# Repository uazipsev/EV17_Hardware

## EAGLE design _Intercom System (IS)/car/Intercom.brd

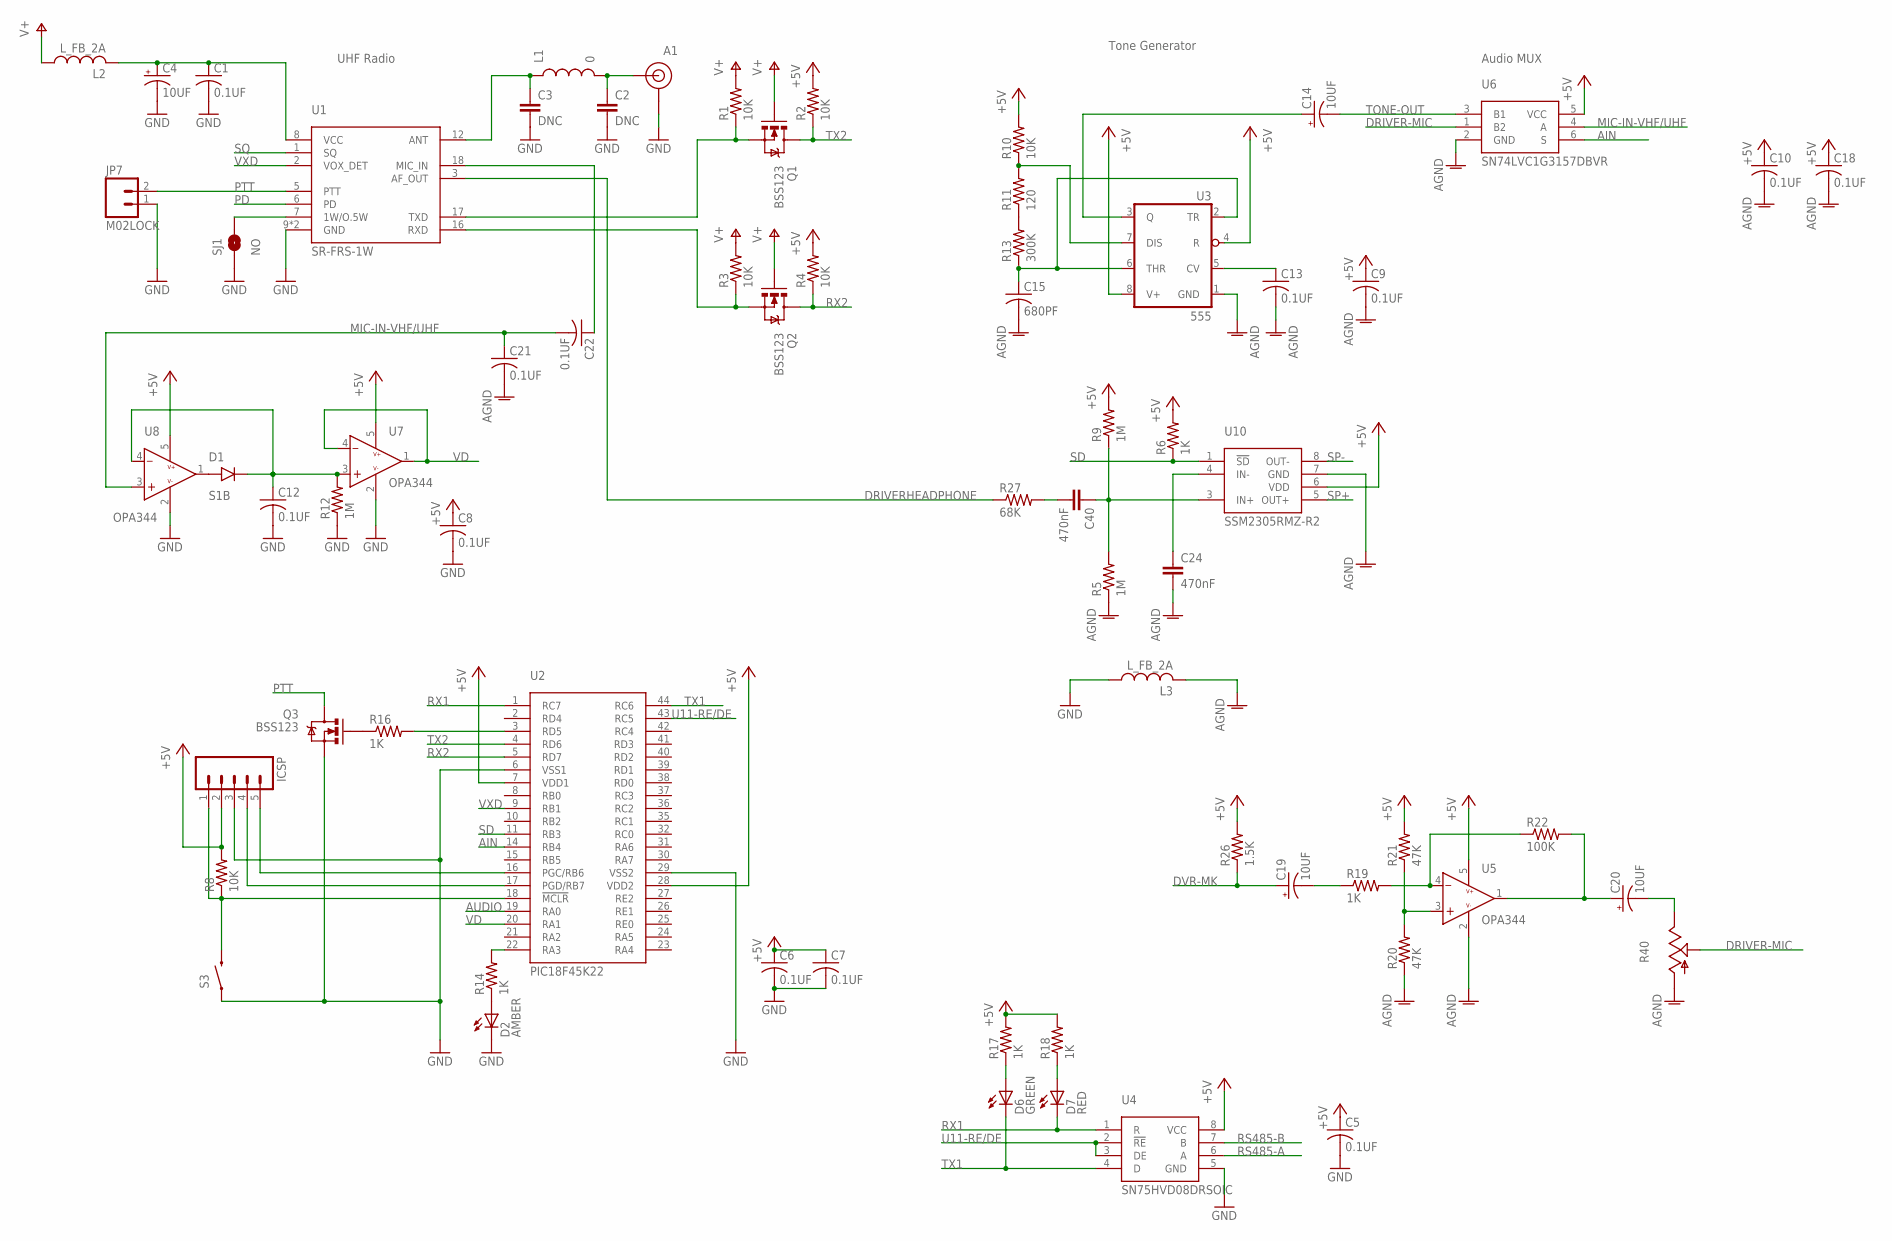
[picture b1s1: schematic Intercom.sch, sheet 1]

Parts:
A1: CONSMA003.062
C1, C5, C6, C7, C8, C9, C10, C12, C13, C18, C21, C22: 0.1UF; 0805
C2, C3: DNC; 0805
C4, C14, C19, C20: 10UF; EIA3216-16V
C15: 680PF; 0805
C24, C40: 470nF; 0805
D1: S1B; SMA
D2: AMBER; CHIP_LED0805
D6: GREEN; CHIP_LED0805
D7: RED; CHIP_LED0805
ICSP: M05LOCK_LONGPADS; 1X05_LOCK_LONGPADS
JP7: M02LOCK; 1X02_LOCK
L1: 0; 1007
L2, L3: L_FB_2A; 0805
Q1, Q2, Q3: BSS123; SOT23
R1, R2, R3, R4, R8, R10: 10K; 0805
R5, R9, R12: 1M; 0805
R6, R14, R16, R17, R18, R19: 1K; 0805
R11: 120; 0805
R13: 300K; 0805
R20, R21: 47K; 0805
R22: 100K; 0805
R26: 1.5K; 0805
R27: 68K; 0805
R40: TRIM_US-CA6H; CA6H
S3: SWITCH-MOMENTARY-2SIDE_EZ; TACTILE-PTH-SIDEEZ
SJ1: NO; SJ_2S-NO
U1: SR-FRS-1W
U2: PIC18F45K22; TQFP-44
U3: 555; SO-8
U4: SN75HVD08DRSOIC; SO-8
U5, U7, U8: OPA344; SOT23-5
U6: SN74LVC1G3157DBVR; SOT23-6
U10: SSM2305RMZ-R2; MSOP-8

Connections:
+5V: C5.1 (+), C6.1 (+), C7.1 (+), C8.1 (+), C9.1 (+), C10.1 (+), C18.1 (+), ICSP.2, R2.2, R4.2, R6.2, R8.2, R9.2, R10.2, R17.2, R18.2, R21.2, R26.2, U2.7 (VDD1), U2.28 (VDD2), U3.4 (R), U3.8 (V+), U4.8 (VCC), U5.5 (V+), U6.5 (VCC), U7.5 (V+), U8.5 (V+), U10.6 (VDD); also elsewhere on the board
AGND: C9.2 (-), C10.2 (-), C13.2 (-), C15.2 (-), C18.2 (-), C21.2 (-), C24.2, L3.2, R5.1, R20.1, R40.A, U3.1 (GND), U5.2 (V-), U6.2 (GND), U10.7 (GND); also elsewhere on the board
AIN: U2.14 (RB4), U6.6 (S)
AUDIO: U2.19 (RA0)
DRIVER-MIC: R40.S, U6.1 (B2)
DRIVERHEADPHONE: R27.1, U1.3 (AF_OUT)
DVR-MK: C19.A (+), R26.1; also elsewhere on the board
GND: A1.G (GND), A1.G1 (GND), A1.G2 (GND), A1.G3 (GND), C1.2 (-), C2.2, C3.2, C4.C (-), C5.2 (-), C6.2 (-), C7.2 (-), C8.2 (-), C12.2 (-), D2.C, ICSP.3, JP7.1, L3.1, Q3.2 (S), R12.1, S3.1, SJ1.1, U1.9 (GND), U1.10 (GND), U2.6 (VSS1), U2.29 (VSS2), U4.5 (GND), U7.2 (V-), U8.2 (V-); also elsewhere on the board
MIC-IN-VHF/UHF: C21.1 (+), C22.2 (-), U6.4 (A), U8.3 (+)
unnamed: C3.1, L1.1, U1.12 (ANT)
unnamed: A1.S (SIGNAL), C2.1, L1.2
unnamed: C1.1 (+), C4.A (+), L2.2, U1.8 (VCC)
unnamed: SJ1.2, U1.7 (1W/O.5W)
unnamed: D1.A, U8.1 (O)
unnamed: C15.1 (+), R13.1, U3.2 (TR), U3.6 (THR)
unnamed: Q2.2 (S), R3.1, U1.16 (RXD)
unnamed: Q1.2 (S), R1.1, U1.17 (TXD)
unnamed: D2.A, R14.1
unnamed: C13.1 (+), U3.5 (CV)
unnamed: R10.1, R11.2, U3.7 (DIS)
unnamed: C24.1, U10.4 (IN-)
unnamed: Q3.1 (G), R16.1
unnamed: R20.2, R21.1, U5.3 (+)
unnamed: C14.A (+), U3.3 (Q)
unnamed: R16.2, U2.3 (RD5)
unnamed: C20.C (-), R40.E
unnamed: C12.1 (+), D1.C, R12.2, U7.3 (+), U8.4 (-)
unnamed: R11.1, R13.2
unnamed: R14.2, U2.22 (RA3)
unnamed: C20.A (+), R22.2, U5.1 (O)
unnamed: R19.2, R22.1, U5.4 (-)
unnamed: C19.C (-), R19.1
unnamed: C40.1, R5.2, R9.1, U10.3 (IN+)
unnamed: ICSP.4, U2.17 (PGD/RB7)
unnamed: ICSP.5, U2.16 (PGC/RB6)
unnamed: C40.2, R27.2
unnamed: ICSP.1, R8.1, S3.2, U2.18 (!MCLR)
unnamed: C22.1 (+), U1.18 (MIC_IN)
unnamed: D7.A, R18.1
unnamed: D6.A, R17.1
PD: U1.6 (PD)
PTT: JP7.2, Q3.3 (D), U1.5 (PTT)
RS485-A: U4.6 (A); also elsewhere on the board
RS485-B: U4.7 (B); also elsewhere on the board
RX1: D7.C, U2.1 (RC7), U4.1 (R)
RX2: Q2.3 (D), R4.1, U2.5 (RD7)
SD: R6.1, U2.11 (RB3), U10.1 (!SD)
SP+: U10.5 (OUT+); also elsewhere on the board
SP-: U10.8 (OUT-); also elsewhere on the board
SQ: U1.1 (SQ)
TONE-OUT: C14.C (-), U6.3 (B1)
TX1: D6.C, U2.44 (RC6), U4.4 (D)
TX2: Q1.3 (D), R2.1, U2.4 (RD6)
U11-RE/DE: U2.43 (RC5), U4.2 (!RE), U4.3 (DE)
V+: L2.1, Q1.1 (G), Q2.1 (G), R1.2, R3.2; also elsewhere on the board
VD: U2.20 (RA1), U7.1 (O), U7.4 (-)
VXD: U1.2 (VOX_DET), U2.9 (RB1)

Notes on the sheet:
UHF Radio
Tone Generator
Audio MUX

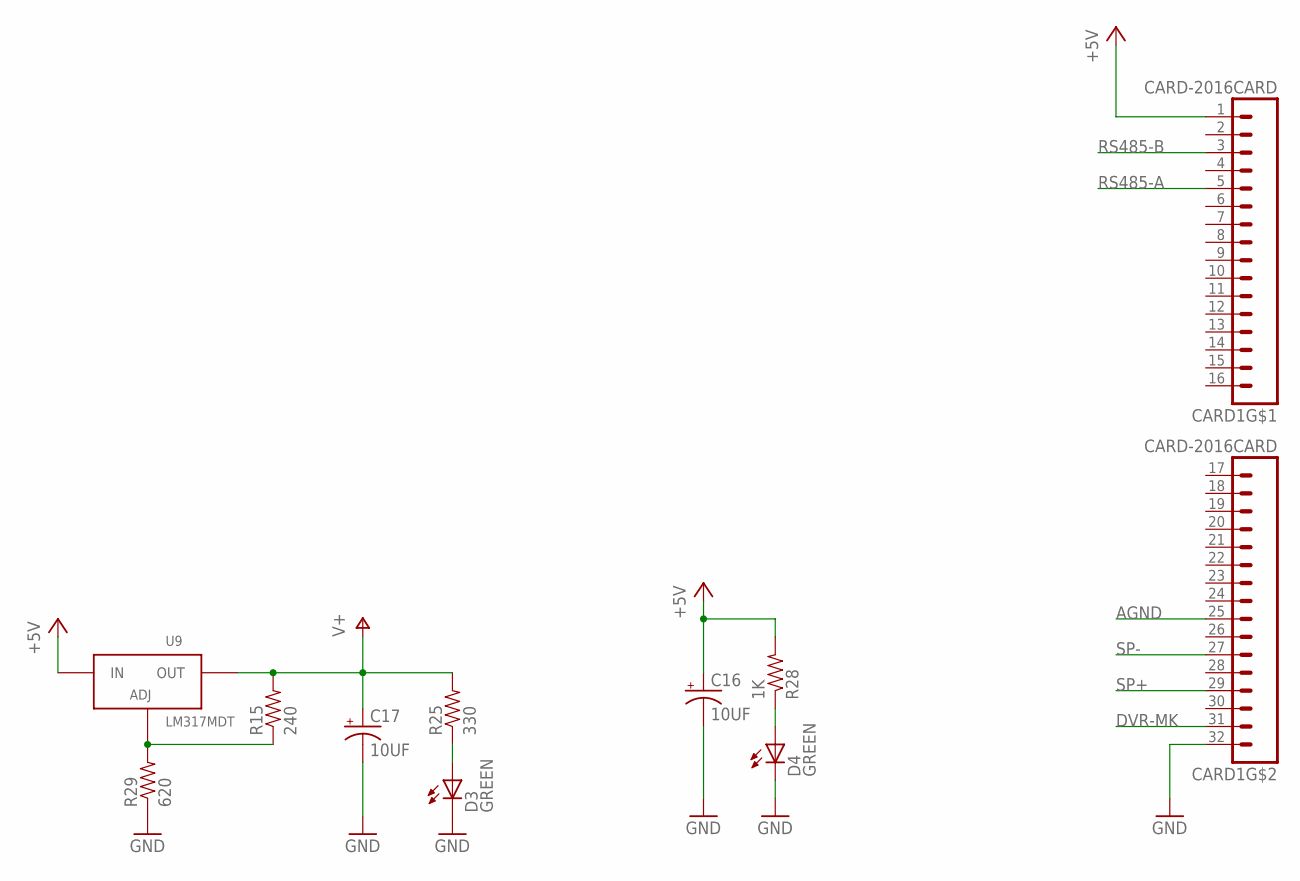
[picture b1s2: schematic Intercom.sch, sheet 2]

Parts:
C16, C17: 10UF; EIA3216-16V
CARD1: CARD-2016CARD; CARD-2016
D3, D4: GREEN; CHIP_LED0805
R15: 240; 0805
R25: 330; 0805
R28: 1K; 0805
R29: 620; 0805
U9: LM317MDT; DPAK

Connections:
+5V: C16.A (+), CARD1.1, R28.2, U9.2 (IN); also elsewhere on the board
AGND: CARD1.25 (9); also elsewhere on the board
DVR-MK: CARD1.31 (15); also elsewhere on the board
GND: C16.C (-), C17.C (-), CARD1.32 (16), D3.C, D4.C, R29.1; also elsewhere on the board
unnamed: R15.1, R29.2, U9.1 (ADJ)
unnamed: D4.A, R28.1
unnamed: D3.A, R25.1
RS485-A: CARD1.5; also elsewhere on the board
RS485-B: CARD1.3; also elsewhere on the board
SP+: CARD1.29 (13); also elsewhere on the board
SP-: CARD1.27 (11); also elsewhere on the board
V+: C17.A (+), R15.2, R25.2, U9.3 (OUT); also elsewhere on the board

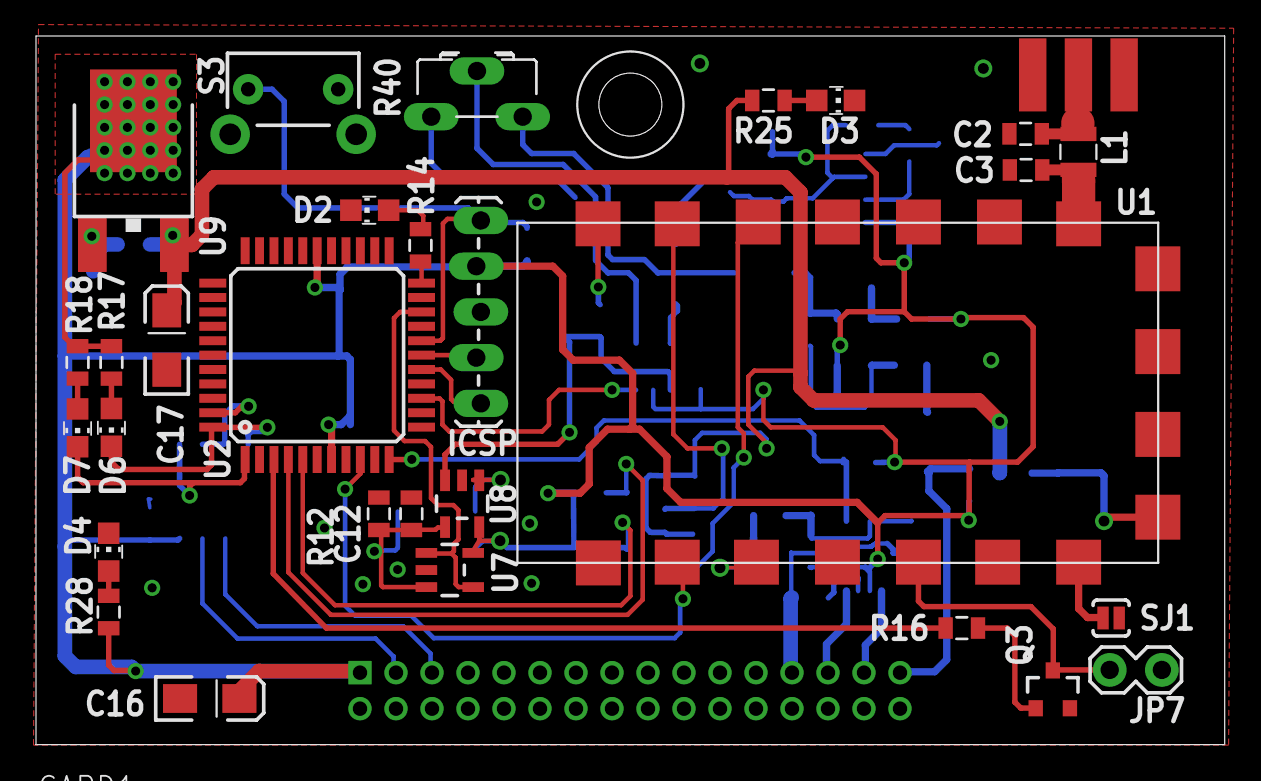
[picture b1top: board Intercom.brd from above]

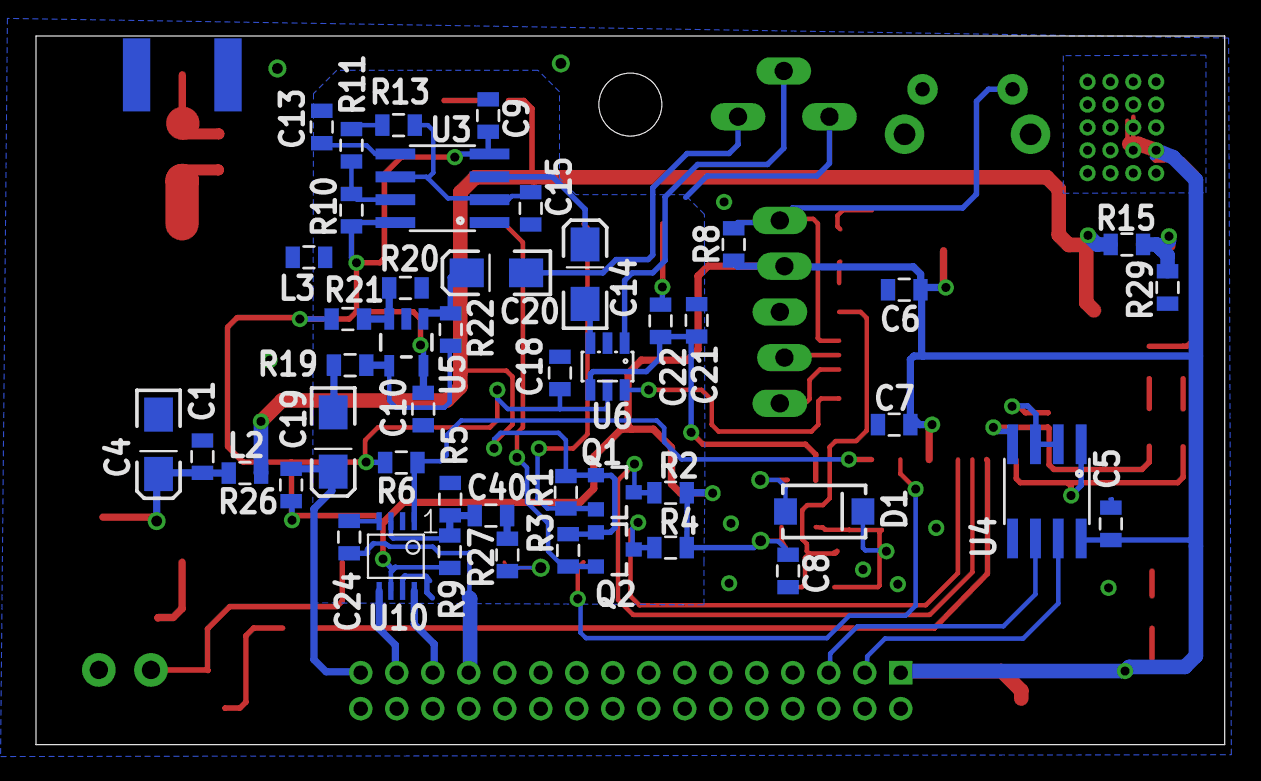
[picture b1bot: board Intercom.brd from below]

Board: 2 copper layers, 66.0 x 39.4 mm, 78 parts (47 on the bottom side), 57 nets.

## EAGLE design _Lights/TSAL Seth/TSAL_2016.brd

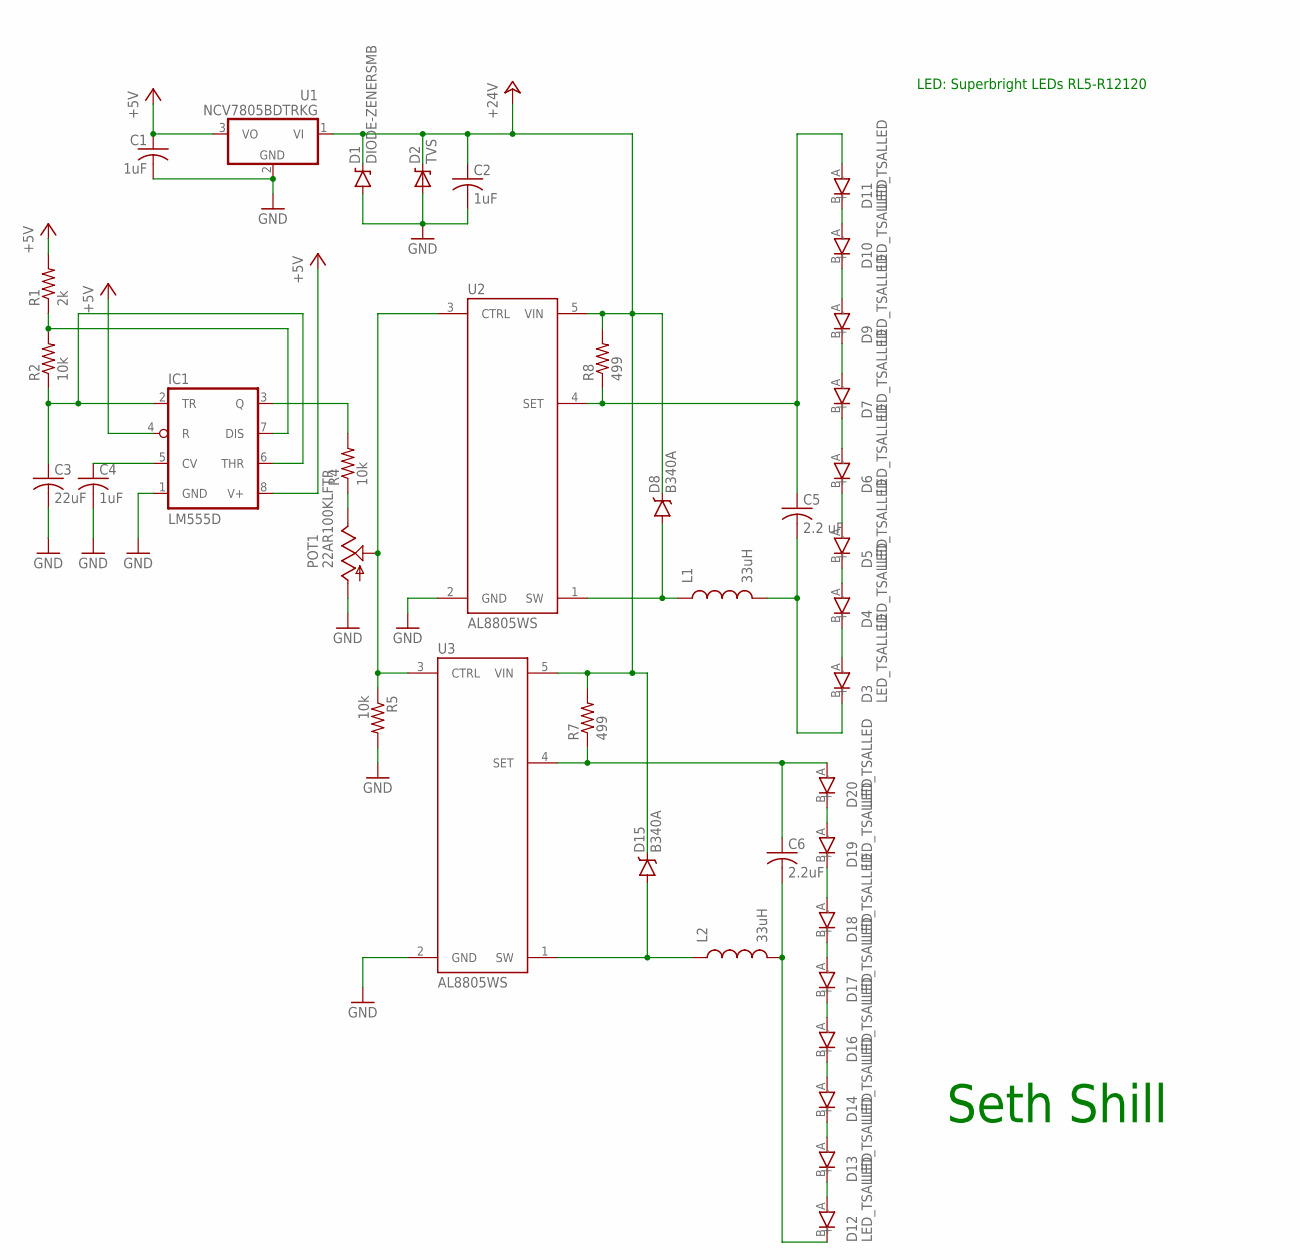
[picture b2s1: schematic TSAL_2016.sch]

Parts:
C1, C2, C4: 1uF; 0805@1
C3: 22uF; 0805@1
C5: 2.2 uF; 0603@1
C6: 2.2uF; 0603@1
D1: DIODE-ZENERSMB; SMB-DIODE
D2: TVS; DO-214AC
D3, D4, D5, D6, D7, D9, D10, D11, D12, D13, D14, D16, D17, D18, D19, D20: LED_TSALLED; LED_TSAL
D8, D15: B340A; SMA-DIODE
IC1: LM555D; SO08
L1, L2: 33uH; 1007
POT1: 22AR100KLFTR
R1: 2k; 0805@1
R2, R4, R5: 10k; 0805@1
R7, R8: 499; 0603@1
U1: NCV7805BDTRKG; DPAK
U2, U3: AL8805WS; SOT23-5

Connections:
+5V: C1.1 (+), IC1.4 (R), IC1.8 (V+), R1.2, U1.3 (VO)
+24V: C2.1 (+), D1.C, D2.C, D8.C, D15.C, R7.2, R8.2, U1.1 (VI), U2.5 (VIN), U3.5 (VIN)
GND: C1.2 (-), C2.2 (-), C3.2 (-), C4.2 (-), D1.A, D2.A, IC1.1 (GND), POT1.3 (CW), R5.2, U1.2 (GND), U2.2 (GND), U3.2 (GND)
unnamed: C6.1 (+), D20.A (+), R7.1, U3.4 (SET)
unnamed: POT1.2 (W), R5.1, U2.3 (CTRL), U3.3 (CTRL)
unnamed: D17.A (+), D18.B (-)
unnamed: C4.1 (+), IC1.5 (CV)
unnamed: IC1.7 (DIS), R1.1, R2.2
unnamed: D15.A, L2.1, U3.1 (SW)
unnamed: C5.1 (+), D11.A (+), R8.1, U2.4 (SET)
unnamed: D10.A (+), D11.B (-)
unnamed: C3.1 (+), IC1.2 (TR), IC1.6 (THR), R2.1
unnamed: D18.A (+), D19.B (-)
unnamed: D9.A (+), D10.B (-)
unnamed: D7.A (+), D9.B (-)
unnamed: C6.2 (-), D12.B (-), L2.2
unnamed: D6.A (+), D7.B (-)
unnamed: D5.A (+), D6.B (-)
unnamed: D19.A (+), D20.B (-)
unnamed: D12.A (+), D13.B (-)
unnamed: C5.2 (-), D3.B (-), L1.2
unnamed: D13.A (+), D14.B (-)
unnamed: D16.A (+), D17.B (-)
unnamed: D14.A (+), D16.B (-)
unnamed: D4.A (+), D5.B (-)
unnamed: D3.A (+), D4.B (-)
unnamed: D8.A, L1.1, U2.1 (SW)
unnamed: POT1.1 (CCW), R4.1
unnamed: IC1.3 (Q), R4.2

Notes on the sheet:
LED: Superbright LEDs RL5-R12120
Seth Shill

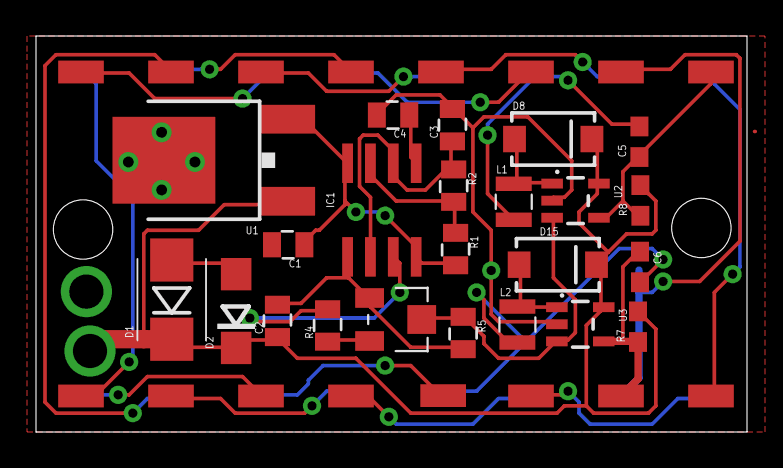
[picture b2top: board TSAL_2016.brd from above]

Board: 2 copper layers, 39.5 x 22.0 mm, 39 parts (0 on the bottom side), 29 nets.

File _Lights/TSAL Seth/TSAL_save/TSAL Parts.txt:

Partlist

Exported from TSAL_3_5_16.brd at 4/21/2016 5:39 PM

EAGLE Version 7.5.0 Copyright (c) 1988-2015 CadSoft

Assembly variant: 

Part     Value          Package      Library       Position (inch)       Orientation

C1       1uF            0805@1       FSAE Electric (0.78181102 0.40614961) R270
C2       1uF            0805@1       FSAE Electric (0.69568504 0.23773228) R90
C3       22uF           0805@1       FSAE Electric (0.825 0.18)          MR0
C4       1uF            0805@1       FSAE Electric (1.16074803 0.35380315) MR270
C5       2.2 uF         0603@1       FSAE Electric (1.56507874 0.31956693) R90
C6       2.2uF          0603@1       FSAE Electric (1.16594488 0.32531496) R90
D1       DIODE-ZENERSMB SMB-DIODE    FSAE Electric (0.4454252 0.28230709) R90
D2       TVS            DO-214AC     FSAE Electric (0.59837008 0.28530709) R90
D3       LED_TSALLED    LED_TSAL     FSAE Electric (1.565 0.55)          R0
D4       LED_TSALLED    LED_TSAL     FSAE Electric (1.765 0.05)          R0
D5       LED_TSALLED    LED_TSAL     FSAE Electric (1.365 0.05)          R0
D6       LED_TSALLED    LED_TSAL     FSAE Electric (0.965 0.05)          R0
D7       LED_TSALLED    LED_TSAL     FSAE Electric (0.565 0.05)          R0
D8       B340A          SMA-DIODE    FSAE Electric (1.81944882 0.34074803) R270
D9       LED_TSALLED    LED_TSAL     FSAE Electric (0.565 0.55)          R0
D10      LED_TSALLED    LED_TSAL     FSAE Electric (0.965 0.55)          R0
D11      LED_TSALLED    LED_TSAL     FSAE Electric (1.365 0.55)          R0
D12      LED_TSALLED    LED_TSAL     FSAE Electric (1.165 0.55)          R0
D13      LED_TSALLED    LED_TSAL     FSAE Electric (1.765 0.55)          R0
D14      LED_TSALLED    LED_TSAL     FSAE Electric (1.565 0.05)          R0
D15      B340A          SMA-DIODE    FSAE Electric (1.4146063 0.34062992) R270
D16      LED_TSALLED    LED_TSAL     FSAE Electric (1.165 0.05)          R0
D17      LED_TSALLED    LED_TSAL     FSAE Electric (0.765 0.05)          R0
D18      LED_TSALLED    LED_TSAL     FSAE Electric (0.365 0.05)          R0
D19      LED_TSALLED    LED_TSAL     FSAE Electric (0.365 0.55)          R180
D20      LED_TSALLED    LED_TSAL     FSAE Electric (0.765 0.55)          R0
IC1      LM555D         SO08         FSAE Electric (0.96795276 0.35325197) MR90
L1       33uH           1007         FSAE Electric (1.68220472 0.45704724) R270
L2       33uH           1007         FSAE Electric (1.28370079 0.44909449) R270
POT1     22AR100KLFTR   22AR100KLFTR FSAE Electric (1.43580315 0.24681102) MR0
R1       2k             0805@1       FSAE Electric (1.085 0.18)          MR180
R2       10k            0805@1       FSAE Electric (0.955 0.18)          MR180
R4       10k            0805@1       FSAE Electric (1.34 0.4)            MR90
R5       10k            0805@1       FSAE Electric (1.55582677 0.26927559) MR270
R7       499            0603@1       FSAE Electric (1.27897638 0.18519685) R0
R8       499            0603@1       FSAE Electric (1.68511811 0.18007874) R0
U1       NCV7805BDTRKG  DPAK         FSAE Electric (0.55689764 0.33707087) MR90
U2       AL8805WS       SOT23-5      FSAE Electric (1.68464567 0.32185039) R180
U3       AL8805WS       SOT23-5      FSAE Electric (1.28429134 0.31141732) R180

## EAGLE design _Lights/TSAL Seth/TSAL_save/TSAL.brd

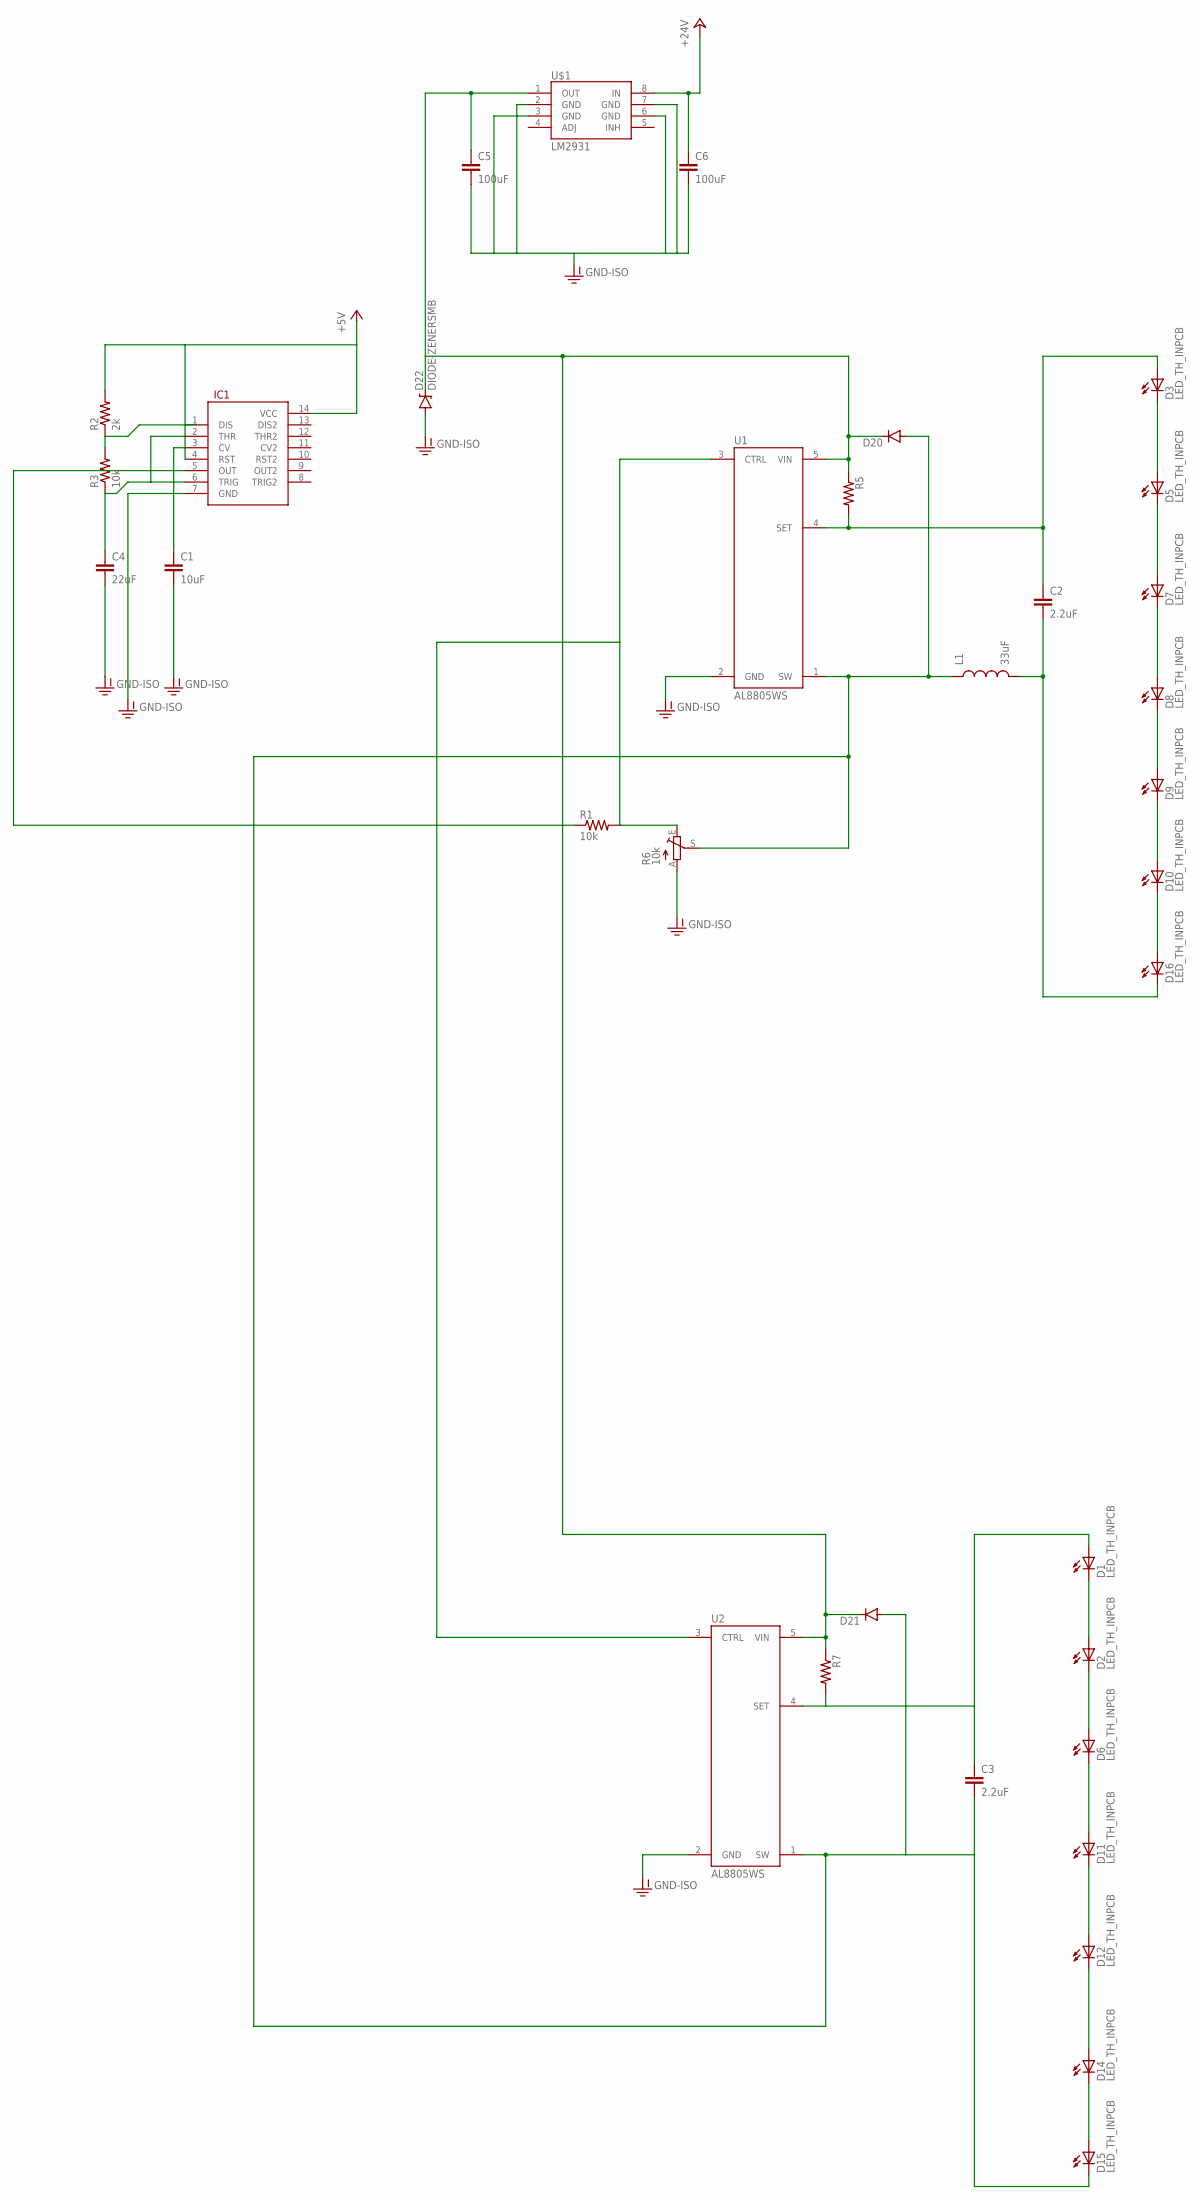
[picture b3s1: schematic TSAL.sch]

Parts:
C1: 10uF; 0805
C2, C3: 2.2uF; 0805
C4: 22uF; 0805
C5, C6: 100uF; 0805
D1, D2, D3, D5, D6, D7, D8, D9, D10, D11, D12, D14, D15, D16: LED_TH_INPCB; 5MM_TH_INDENT
D20, D21: DIODESMB; SMB-DIODE
D22: DIODE-ZENERSMB; SMB-DIODE
IC1: 556; DIL14
L1: 33uF; 0805
R1, R3: 10k; 0805
R2: 2k; 0805
R5, R7: RESISTOR0805-RES; 0805
R6: 10k; B25P
U1, U2: AL8805WS; SOT23-5
U$1: LM2931; SO08

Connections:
+5V: IC1.4 (RST), IC1.14 (VCC), R2.2
+24V: C6.1, U$1.8 (IN)
GND-ISO: C1.2, C4.2, C5.2, C6.2, D22.A, IC1.7 (GND), R6.A, U1.2 (GND), U2.2 (GND), U$1.2 (GND), U$1.3 (GND), U$1.6 (GND), U$1.7 (GND)
unnamed: C3.1, D1.A, R7.2, U2.4 (SET)
unnamed: IC1.5 (OUT), R1.1
unnamed: D14.C, D15.A
unnamed: C1.1, IC1.3 (CV)
unnamed: R2.1, R3.2
unnamed: D12.C, D14.A
unnamed: C3.2, D15.C, D20.A, D21.A, L1.1, R6.S, U1.1 (SW), U2.1 (SW)
unnamed: D3.C, D5.A
unnamed: C4.1, IC1.2 (THR), IC1.6 (TRIG), R3.1
unnamed: D11.C, D12.A
unnamed: D6.C, D11.A
unnamed: D2.C, D6.A
unnamed: R1.2, R6.E, U1.3 (CTRL), U2.3 (CTRL)
unnamed: D1.C, D2.A
unnamed: C2.1, D3.A, R5.2, U1.4 (SET)
unnamed: D10.C, D16.A
unnamed: C2.2, D16.C, L1.2
unnamed: D9.C, D10.A
unnamed: D8.C, D9.A
unnamed: D7.C, D8.A
unnamed: D5.C, D7.A
unnamed: C5.1, D20.C, D21.C, D22.C, R5.1, R7.1, U1.5 (VIN), U2.5 (VIN), U$1.1 (OUT)

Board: 2 copper layers, 34 parts (0 on the bottom side), 25 nets, no tracks yet.

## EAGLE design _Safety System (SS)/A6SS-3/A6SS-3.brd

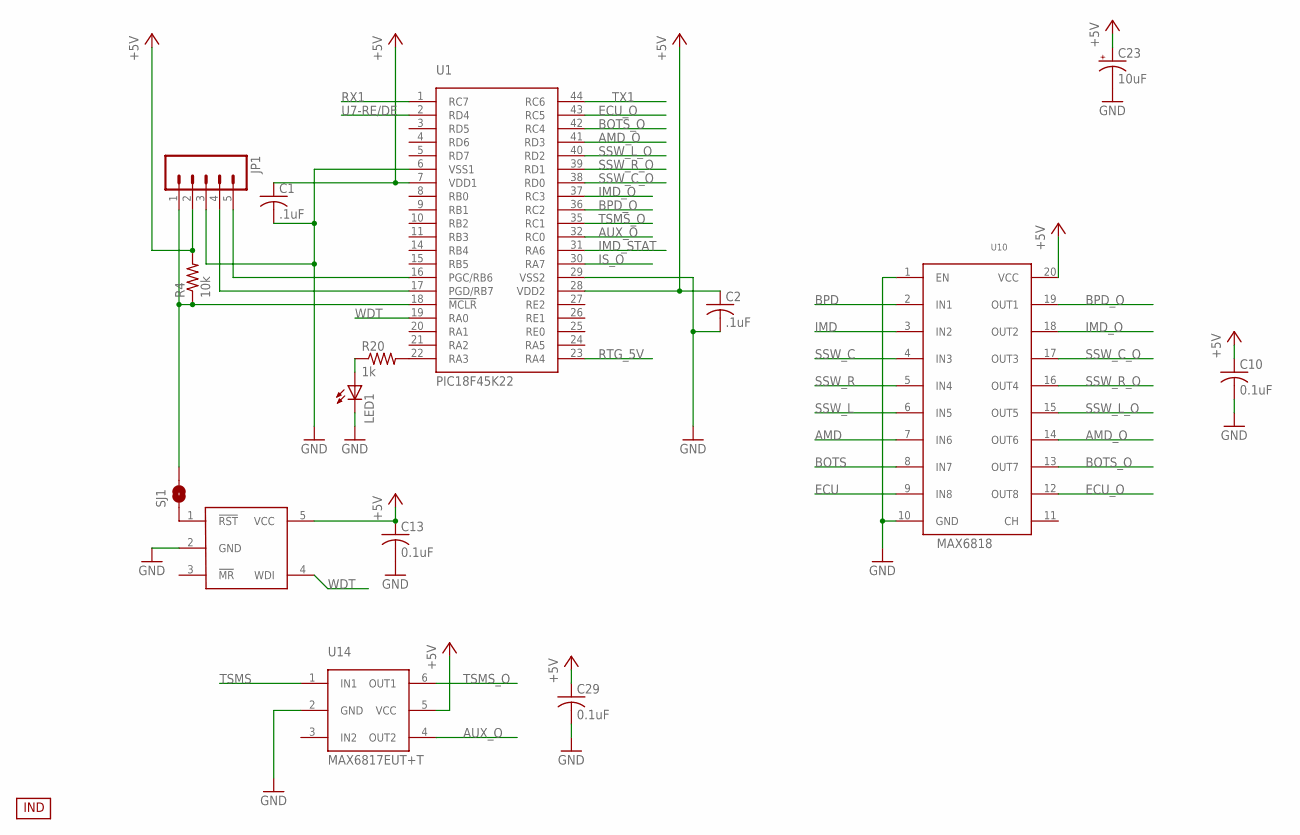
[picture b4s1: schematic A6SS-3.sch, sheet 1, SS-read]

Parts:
C1, C2: .1uF; C0603
C10, C13, C29: 0.1uF; C0603
C23: 10uF; EIA3216
JP1: M05LOCK_LONGPADS; 1X05_LOCK_LONGPADS
LED1: LEDCHIPLED_0603; CHIPLED_0603
R4: 10k; 0603-RES
R20: 1k; R0603
SJ1: SOLDERJUMPERNO; SJ_2S-NO
U1: PIC18F45K22; TQFP-44
U10: MAX6818; SSOP-20
U14: MAX6817EUT+T; SOT23-6
U15: MAX823; SOT23-5L
U$1: INDPK1; PICKIT-PIN-1

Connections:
+5V: C1.1, C2.1, C10.1, C13.1, C23.A (+), C29.1, JP1.2, R4.2, U1.7 (VDD1), U1.28 (VDD2), U10.20 (VCC), U14.5 (VCC), U15.5 (VCC); also elsewhere on the board
AMD: U10.7 (IN6); also elsewhere on the board
AMD_O: U1.41 (RD3), U10.14 (OUT6)
AUX_O: U1.32 (RC0), U14.4 (OUT2)
BOTS: U10.8 (IN7); also elsewhere on the board
BOTS_O: U1.42 (RC4), U10.13 (OUT7)
BPD: U10.2 (IN1); also elsewhere on the board
BPD_O: U1.36 (RC2), U10.19 (OUT1)
ECU: U10.9 (IN8); also elsewhere on the board
ECU_O: U1.43 (RC5), U10.12 (OUT8)
GND: C1.2, C2.2, C10.2, C13.2, C23.C (-), C29.2, JP1.3, LED1.C, U1.6 (VSS1), U1.29 (VSS2), U10.1 (EN), U10.10 (GND), U14.2 (GND), U15.2 (GND); also elsewhere on the board
IMD: U10.3 (IN2); also elsewhere on the board
IMD_O: U1.37 (RC3), U10.18 (OUT2)
IMD_STAT: U1.31 (RA6); also elsewhere on the board
IS_O: U1.30 (RA7); also elsewhere on the board
unnamed: SJ1.1, U15.1 (!RST)
unnamed: LED1.A, R20.1
unnamed: R20.2, U1.22 (RA3)
unnamed: JP1.4, U1.17 (PGD/RB7)
unnamed: JP1.5, U1.16 (PGC/RB6)
unnamed: JP1.1, R4.1, SJ1.2, U1.18 (!MCLR)
RTG_5V: U1.23 (RA4); also elsewhere on the board
RX1: U1.1 (RC7); also elsewhere on the board
SSW_C: U10.4 (IN3); also elsewhere on the board
SSW_C_O: U1.38 (RD0), U10.17 (OUT3)
SSW_L: U10.6 (IN5); also elsewhere on the board
SSW_L_O: U1.40 (RD2), U10.15 (OUT5)
SSW_R: U10.5 (IN4); also elsewhere on the board
SSW_R_O: U1.39 (RD1), U10.16 (OUT4)
TSMS: U14.1 (IN1); also elsewhere on the board
TSMS_O: U1.35 (RC1), U14.6 (OUT1)
TX1: U1.44 (RC6); also elsewhere on the board
U7-RE/DE: U1.2 (RD4); also elsewhere on the board
WDT: U1.19 (RA0), U15.4 (WDI)

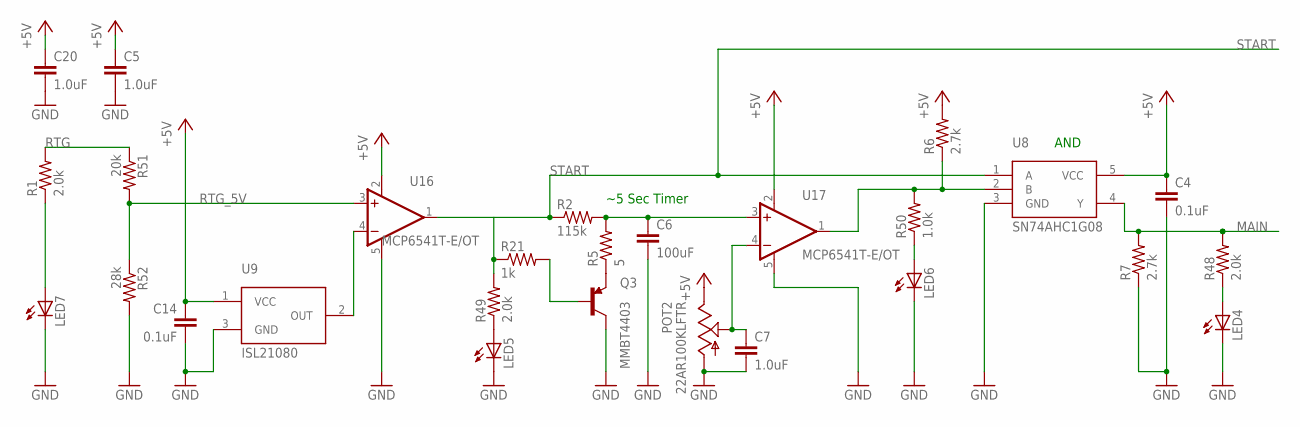
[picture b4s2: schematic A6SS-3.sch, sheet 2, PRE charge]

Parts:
C4, C14: 0.1uF; 0603-CAP
C5: 1.0uF; 0603-CAP
C6: 100uF; 1206
C7, C20: 1.0uF; 0805
LED4, LED5, LED6, LED7: LEDCHIPLED_0603; CHIPLED_0603
POT2: 22AR100KLFTR
Q3: MMBT4403; SOT23
R1, R48, R49: 2.0k; 0603-RES
R2: 115k; 1206
R5: 5; 0603-RES
R6, R7: 2.7k; 0603-RES
R21: 1k; 0603-RES
R50: 1.0k; 0603-RES
R51: 20k; 0603-RES
R52: 28k; 0603-RES
U8: SN74AHC1G08; SOT23-5
U9: ISL21080; SOT-23
U16, U17: MCP6541T-E/OT; SOT23-5

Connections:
+5V: C4.1, C5.1, C14.1, C20.1, POT2.1 (CCW), R6.2, U8.5 (VCC), U9.1 (VCC), U16.2 (V-), U17.2 (V-); also elsewhere on the board
GND: C4.2, C5.2, C6.2, C7.2, C14.2, C20.2, LED4.C, LED5.C, LED6.C, LED7.C, POT2.3 (CW), Q3.3 (C), R7.1, R52.2, U8.3 (GND), U9.3 (GND), U16.5 (V+), U17.5 (V+); also elsewhere on the board
MAIN: R7.2, R48.2, U8.4 (Y); also elsewhere on the board
unnamed: C7.1, POT2.2 (W), U17.4 (-IN)
unnamed: Q3.1 (B), R21.2
unnamed: Q3.2 (E), R5.1
unnamed: U9.2 (OUT), U16.4 (-IN)
unnamed: LED7.A, R1.1
unnamed: C6.1, R2.2, R5.2, U17.3 (+IN)
unnamed: R6.1, R50.2, U8.2 (B), U17.1 (OUT)
unnamed: LED4.A, R48.1
unnamed: LED5.A, R49.1
unnamed: LED6.A, R50.1
RTG: R1.2, R51.1; also elsewhere on the board
RTG_5V: R51.2, R52.1, U16.3 (+IN); also elsewhere on the board
START: R2.1, R21.1, R49.2, U8.1 (A), U16.1 (OUT); also elsewhere on the board

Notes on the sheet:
~5 Sec Timer
AND

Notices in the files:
parts and their libraries:
SparkFun-Passives: Licensing: CC v3.0 Share-Alike You are welcome to use this library for commercial purposes.
SparkFun-PowerIC: Licensing: Creative Commons ShareAlike 4.0 International - https://creativecommons.org/licenses/by-sa/4.0
